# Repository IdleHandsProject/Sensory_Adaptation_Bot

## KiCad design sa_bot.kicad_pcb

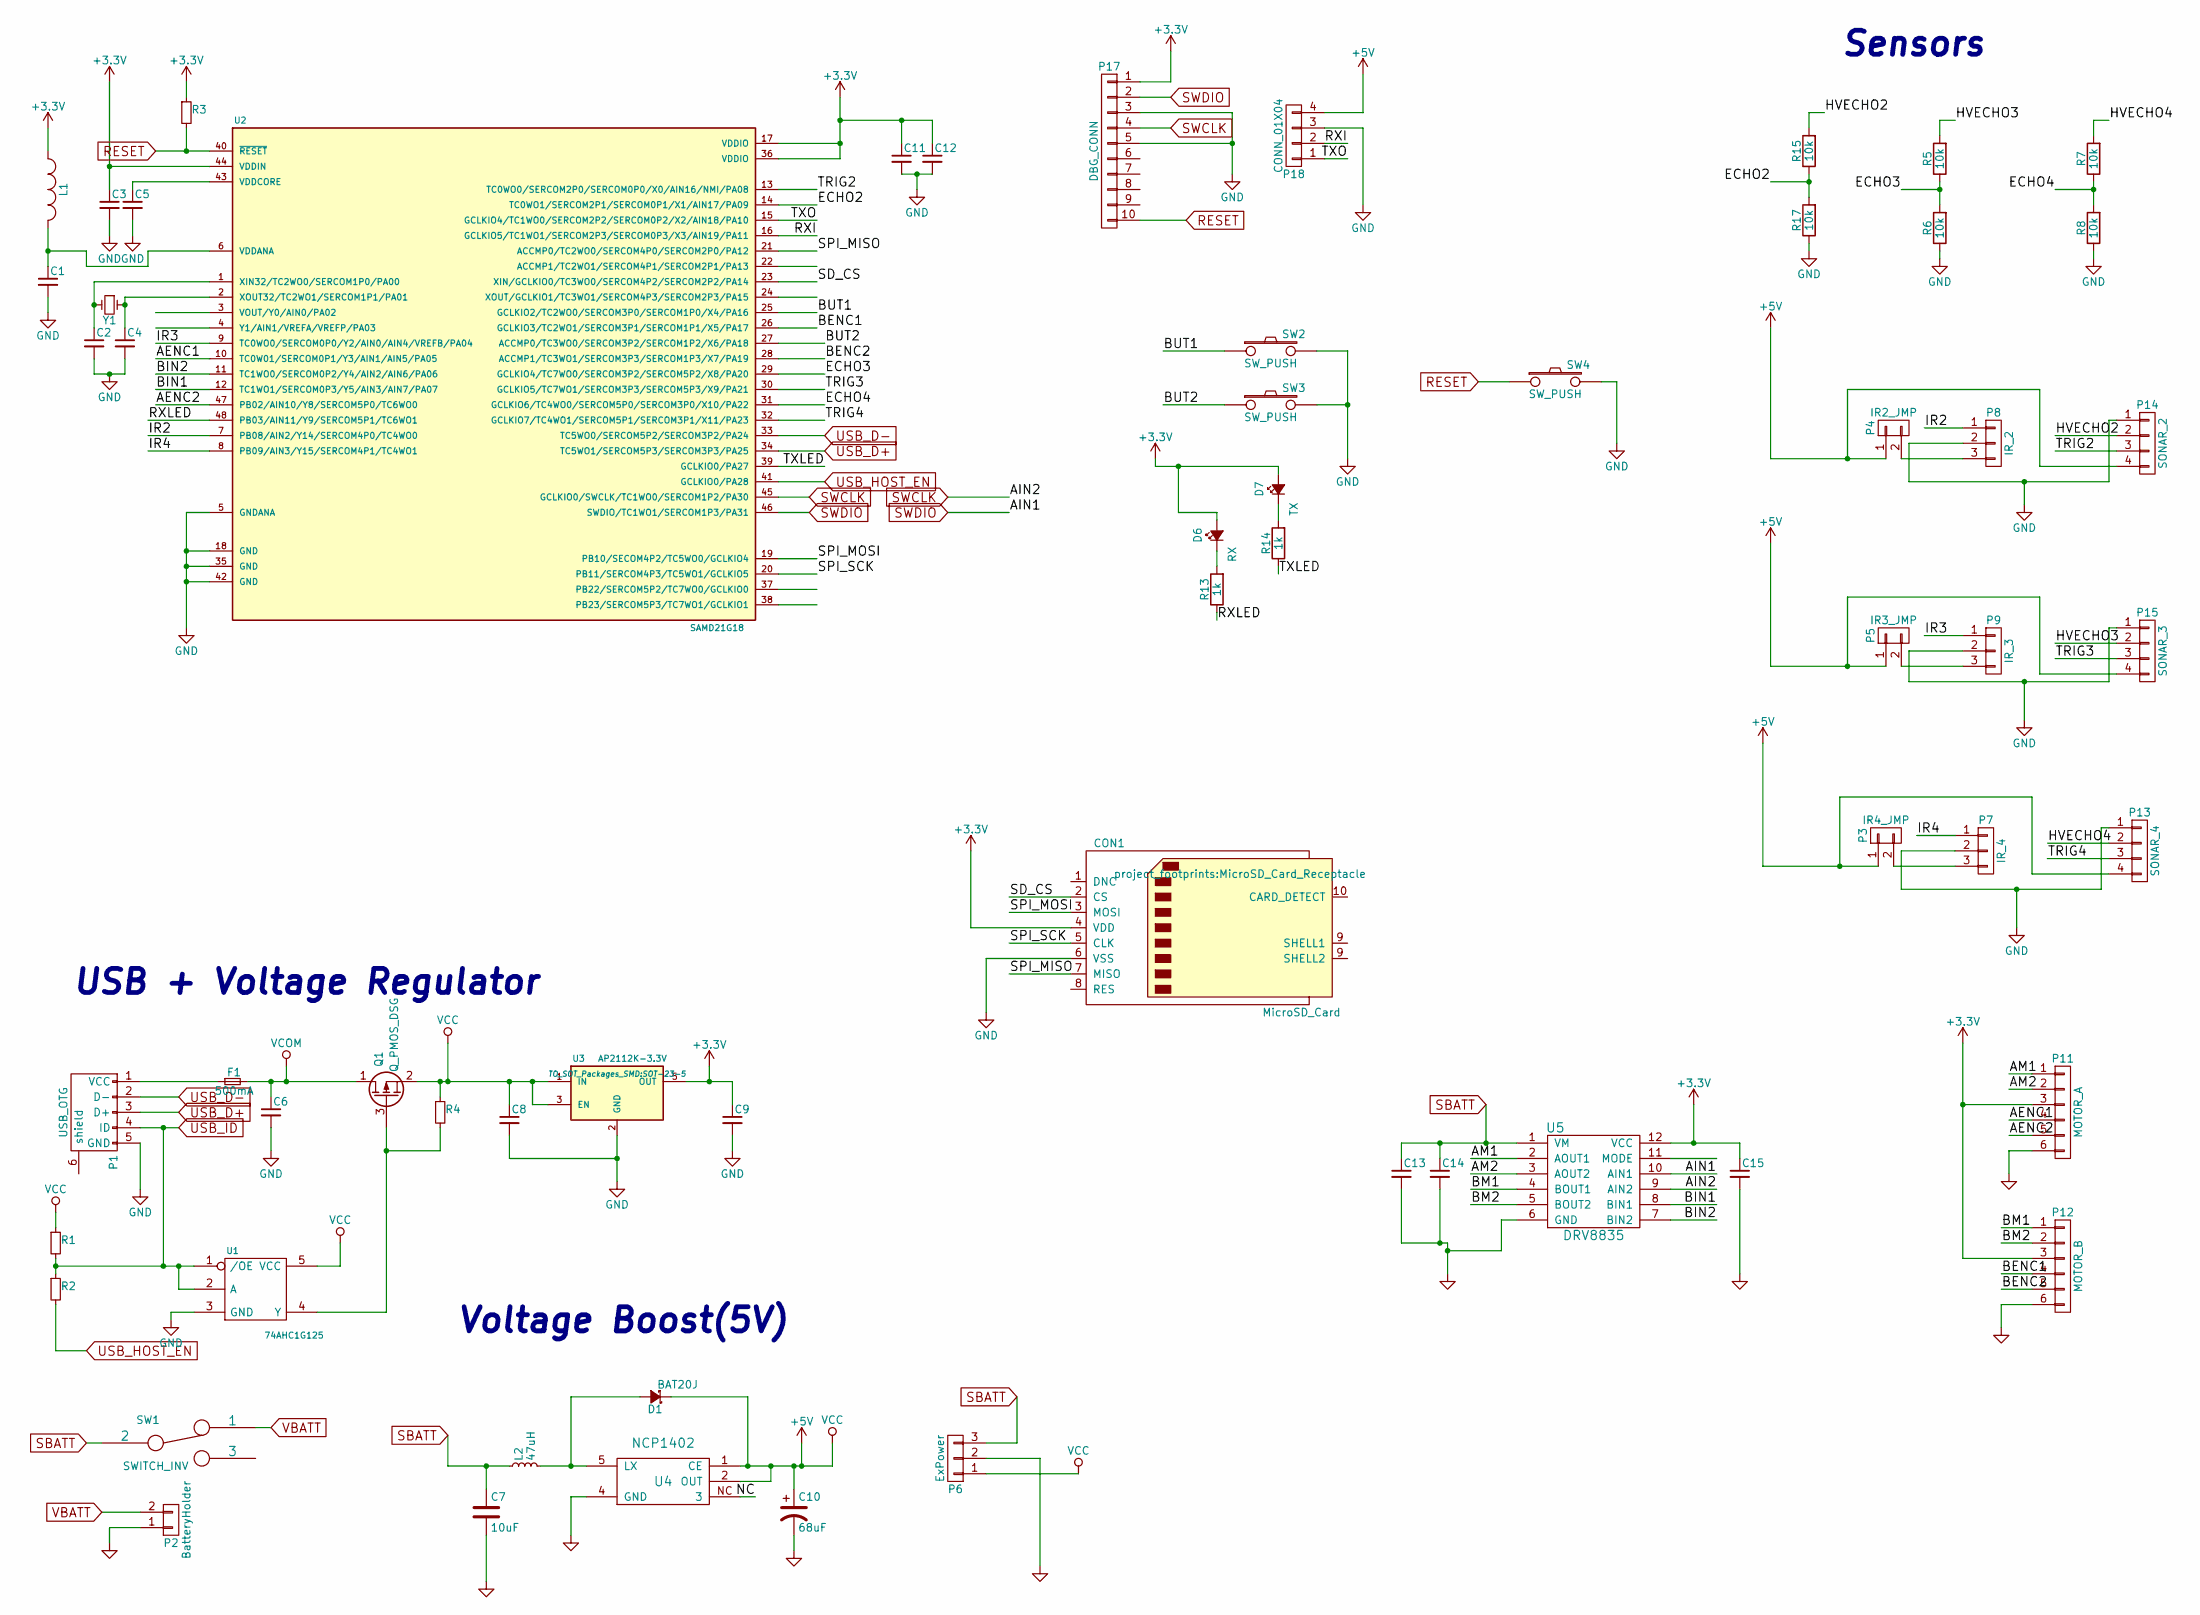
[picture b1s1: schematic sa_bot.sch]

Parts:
C1, C3, C5, C11, C12, C14, C15: 0.1uF; C_0402_Hand; Digikey Part No. 490-6328-1-ND
C2, C4: 15pF; C_0402_Hand; Digikey Part No. 712-1261-1-ND
C6: 2.2uF; C_0402_Hand; Digikey Part No. 1276-1291-1-ND
C7: 10uF; C_0402_Hand; Digikey Part No. 311-1376-1-ND
C8: 1uF; C_0402_Hand; Digikey Part No. 490-4516-1-ND
C9: 2.2uF; C_0402_Hand; Digikey Part No. 587-1059-1-ND
C10: 68uF; C_0402_Hand; Digikey Part No. P16816-1-ND
C13: 10uF; C_0402_Hand; Digikey Part No. 311-1729-1-ND
CON1: MicroSD_Card; MicroSD_Card_Receptacle; Digikey Part No. 114-00841-68-2-ND
D1: BAT20J; sod80c; Digikey Part No. 497-3381-1-ND
D6: RX; Led_0603; Digikey Part No. 160-1447-1-ND
D7: TX; Led_0603; Digikey Part No. 160-1448-1-ND
F1: 500mA; c_1206; Digikey Part No. 507-1803-1-ND
L1: FB - 30Ohm; R_SM0603; Digikey Part No. 445-2986-1-ND
L2: 47uH; I_1212; Digikey Part No. 587-2104-1-ND
P1: USB_OTG; USB_Micro-B; Digikey Part No. 609-4618-1-ND
P2: BatteryHolder; Battery_3xAAA_Holder; Digikey Part No. 36-2479-ND
P3: IR4_JMP; Pin_Header_Straight_1x02
P4: IR2_JMP; Pin_Header_Straight_1x02
P5: IR3_JMP; Pin_Header_Straight_1x02
P6: ExPower; Pin_Header_Straight_1x03
P7: IR_4; Pin_Header_Straight_1x03
P8: IR_2; Pin_Header_Straight_1x03
P9: IR_3; Pin_Header_Straight_1x03
P11: MOTOR_A; Pin_Header_Straight_1x06
P12: MOTOR_B; Pin_Header_Straight_1x06
P13: SONAR_4; Pin_Header_Straight_1x04; Digikey Part No. S5479-ND
P14: SONAR_2; Pin_Header_Straight_1x04; Digikey Part No. S5479-ND
P15: SONAR_3; Pin_Header_Straight_1x04; Digikey Part No. S5479-ND
P17: DBG_CONN; Pin_Header_Straight_2x05_Pitch1.27mm; Digikey Part No. 1175-1627-ND
P18: CONN_01X04; Pin_Header_Straight_1x04
Q1: Q_PMOS_DSG; SOT23; Digikey Part No. DMG2307L-7DICT-ND
R1: 100k; R_0402_Hand; Digikey Part No. 311-100KLRCT-ND
R2: 330; R_0402_Hand; Digikey Part No. 311-330JRCT-ND
R3, R5, R6, R7, R8, R15, R17: 10k; R_0402_Hand; Digikey Part No. 311-10KJRCT-ND
R4: 47K; R_0402_Hand; Digikey Part No. 311-47.0KLRCT-ND
R13, R14: 1k; R_0402_Hand; Digikey Part No. 311-1.0KJRCT-ND
SW1: SWITCH_INV; Pin_Header_Straight_1x03
SW2: SW_PUSH; SW_SPST_PTS645; Digikey Part No. CKN9112CT-ND
SW3: SW_PUSH; SW_SPST_PTS645; Digikey Part No. CKN9084CT-ND
SW4: SW_PUSH; SW_SPST_EVQPE1; Digikey Part No. CKN9084CT-ND
U1: 74AHC1G125; sot23-5; Digikey Part No. 568-4452-1-ND
U2: SAMD21G18; TQFP-48_7x7mm_Pitch0.5mm; Digikey Part No. ATSAMD21G18A-AU-ND
U3: AP2112K-3.3V; SOT-23-5; Digikey Part No. AP2112K-3.3TRG1DICT-ND
U4: NCP1402; sot23-5
U5: DRV8835; WSON-12-2x3; Digikey Part No. 296-30391-1-ND
Y1: Crystal_Small; crystal_smd_5x3.2mm; Digikey Part No. 535-9536-1-ND

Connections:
+3V3: C3.1, C9.1, C11.1, C12.1, C15.1, CON1.4 (VDD), D6.2 (A), D7.2 (A), L1.1, P11.3, P12.3, P17.1, R3.1, U2.17 (VDDIO), U2.36 (VDDIO), U2.44 (VDDIN), U3.5 (OUT), U5.12 (VCC)
/AENC1: P11.4, U2.10 (TC0W01/SERCOM0P1/Y3/AIN1/AIN5/PA05)
/AENC2: P11.5, U2.47 (PB02/AIN10/Y8/SERCOM5P0/TC6WO0)
/AM1: P11.1, U5.2 (AOUT1)
/AM2: P11.2, U5.3 (AOUT2)
/BENC1: P12.4, U2.26 (GCLKIO3/TC2WO1/SERCOM3P1/SERCOM1P1/X5/P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)
/BENC2: P12.5, U2.28 (ACCMP1/TC3WO1/SERCOM3P3/SERCOM1P3/X7/PA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)
/BIN1: U2.12 (TC1WO1/SERCOM0P3/Y5/AIN3/AIN7/PA07), U5.8 (BIN1)
/BIN2: U2.11 (TC1WO0/SERCOM0P2/Y4/AIN2/AIN6/PA06), U5.7 (BIN2)
/BM1: P12.1, U5.4 (BOUT1)
/BM2: P12.2, U5.5 (BOUT2)
/BUT1: SW2.1, U2.25 (GCLKIO2/TC2WO0/SERCOM3P0/SERCOM1P0/X4/P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)
/BUT2: SW3.1, U2.27 (ACCMP0/TC3WO0/SERCOM3P2/SERCOM1P2/X6/PA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)
/ECHO2: R15.1, R17.2, U2.14 (TC0WO1/SERCOM2P1/SERCOM0P1/X1/AIN17/PA09)
/ECHO3: R5.1, R6.2, U2.29 (GCLKIO4/TC7WO0/SERCOM3P2/SERCOM5P2/X8/P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)
/ECHO4: R7.1, R8.2, U2.31 (GCLKIO6/TC4WO0/SERCOM5P0/SERCOM3P0/X10/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)
/HVECHO2: P14.2, R15.2
/HVECHO3: P15.2, R5.2
/HVECHO4: P13.2, R7.2
/IR2: P8.1, U2.7 (PB08/AIN2/Y14/SERCOM4P0/TC4WO0)
/IR3: P9.1, U2.9 (TC0WO0/SERCOM0P0/Y2/AIN0/AIN4/VREFB/PA04)
/IR4: P7.1, U2.8 (PB09/AIN3/Y15/SERCOM4P1/TC4WO1)
/RXI: P18.2, U2.16 (GCLKIO5/TC1WO1/SERCOM2P3/SERCOM0P3/X3/A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)
/RXLED: R13.1, U2.48 (PB03/AIN11/Y9/SERCOM5P1/TC6WO1)
/SD_CS: CON1.2 (CS), U2.23 (XIN/GCLKIO0/TC3WO0/SERCOM4P2/SERCOM2P2/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)
/SPI_MISO: CON1.7 (MISO), U2.21 (ACCMP0/TC2WO0/SERCOM4P0/SERCOM2P0/PA12)
/SPI_MOSI: CON1.3 (MOSI), U2.19 (PB10/SECOM4P2/TC5WO0/GCLKIO4)
/SPI_SCK: CON1.5 (CLK), U2.20 (PB11/SERCOM4P3/TC5WO1/GCLKIO5)
/TRIG2: P14.3, U2.13 (TC0WO0/SERCOM2P0/SERCOM0P0/X0/AIN16/NMI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)
/TRIG3: P15.3, U2.30 (GCLKIO5/TC7WO1/SERCOM3P3/SERCOM5P3/X9/P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)
/TRIG4: P13.3, U2.32 (GCLKIO7/TC4WO1/SERCOM5P1/SERCOM3P1/X11/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)
/TXLED: R14.1, U2.39 (GCLKIO0/PA27)
/TXO: P18.1, U2.15 (GCLKIO4/TC1WO0/SERCOM2P2/SERCOM0P2/X2/A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)
GND: C1.2, C2.2, C3.2, C4.2, C5.2, C6.2, C7.2, C8.2, C9.2, C10.2, C11.2, C12.2, C13.2, C14.2, C15.2, CON1.6 (VSS), P1.5 (GND), P2.1, P6.2, P7.2, P8.2, P9.2, P11.6, P12.6, P13.1, P14.1, P15.1, P17.3, P17.5, P18.3, R6.1, R8.1, R17.1, SW2.2, SW3.2, SW4.2, U1.3 (GND), U2.5 (GNDANA), U2.18 (GND), U2.35 (GND), U2.42 (GND), U3.2 (GND), U4.4 (GND), U5.6 (GND)
unnamed: C1.1, L1.2, U2.6 (VDDANA)
unnamed: C2.1, U2.1 (XIN32/TC2WO0/SERCOM1P0/PA00), Y1.2
unnamed: C4.1, U2.2 (XOUT32/TC2WO1/SERCOM1P1/PA01), Y1.1
unnamed: C5.1, U2.43 (VDDCORE)
unnamed: D1.2 (A), L2.2, U4.5 (LX)
unnamed: D6.1 (K), R13.2
unnamed: D7.1 (K), R14.2
unnamed: F1.1, P1.1 (VCC)
unnamed: P3.2, P7.3
unnamed: P4.2, P8.3
unnamed: P5.2, P9.3
unnamed: Q1.3 (G), R4.2, U1.4 (Y)
RESET: P17.10, R3.2, SW4.1, U2.40 (~RESET~)
SBATT: C7.1, C13.1, C14.1, L2.1, P6.3, SW1.2, U5.1 (VM)
SWDIO: P17.2, U2.46 (SWDIO/TC1WO1/SERCOM1P3/PA31), U5.10 (AIN1)
USB_D+: P1.3 (D+), U2.34 (TC5WO1/SERCOM5P3/SERCOM3P3/PA25)
USB_D-: P1.2 (D-), U2.33 (TC5WO0/SERCOM5P2/SERCOM3P2/PA24)
USB_HOST_EN: R2.2, U2.41 (GCLKIO0/PA28)
USB_ID: P1.4 (ID), R1.2, R2.1, U1.1 (/OE), U1.2 (A)
VBATT: P2.2, SW1.1
VCC: C8.1, C10.1, D1.1 (K), P3.1, P4.1, P5.1, P6.1, P13.4, P14.4, P15.4, P18.4, Q1.2 (S), R1.1, R4.1, U1.5 (VCC), U3.1 (IN), U3.3 (EN), U4.1 (CE), U4.2 (OUT)
VCOM: C6.1, F1.2, Q1.1 (D)

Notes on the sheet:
USB + Voltage Regulator
Voltage Boost(5V)
Sensors

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
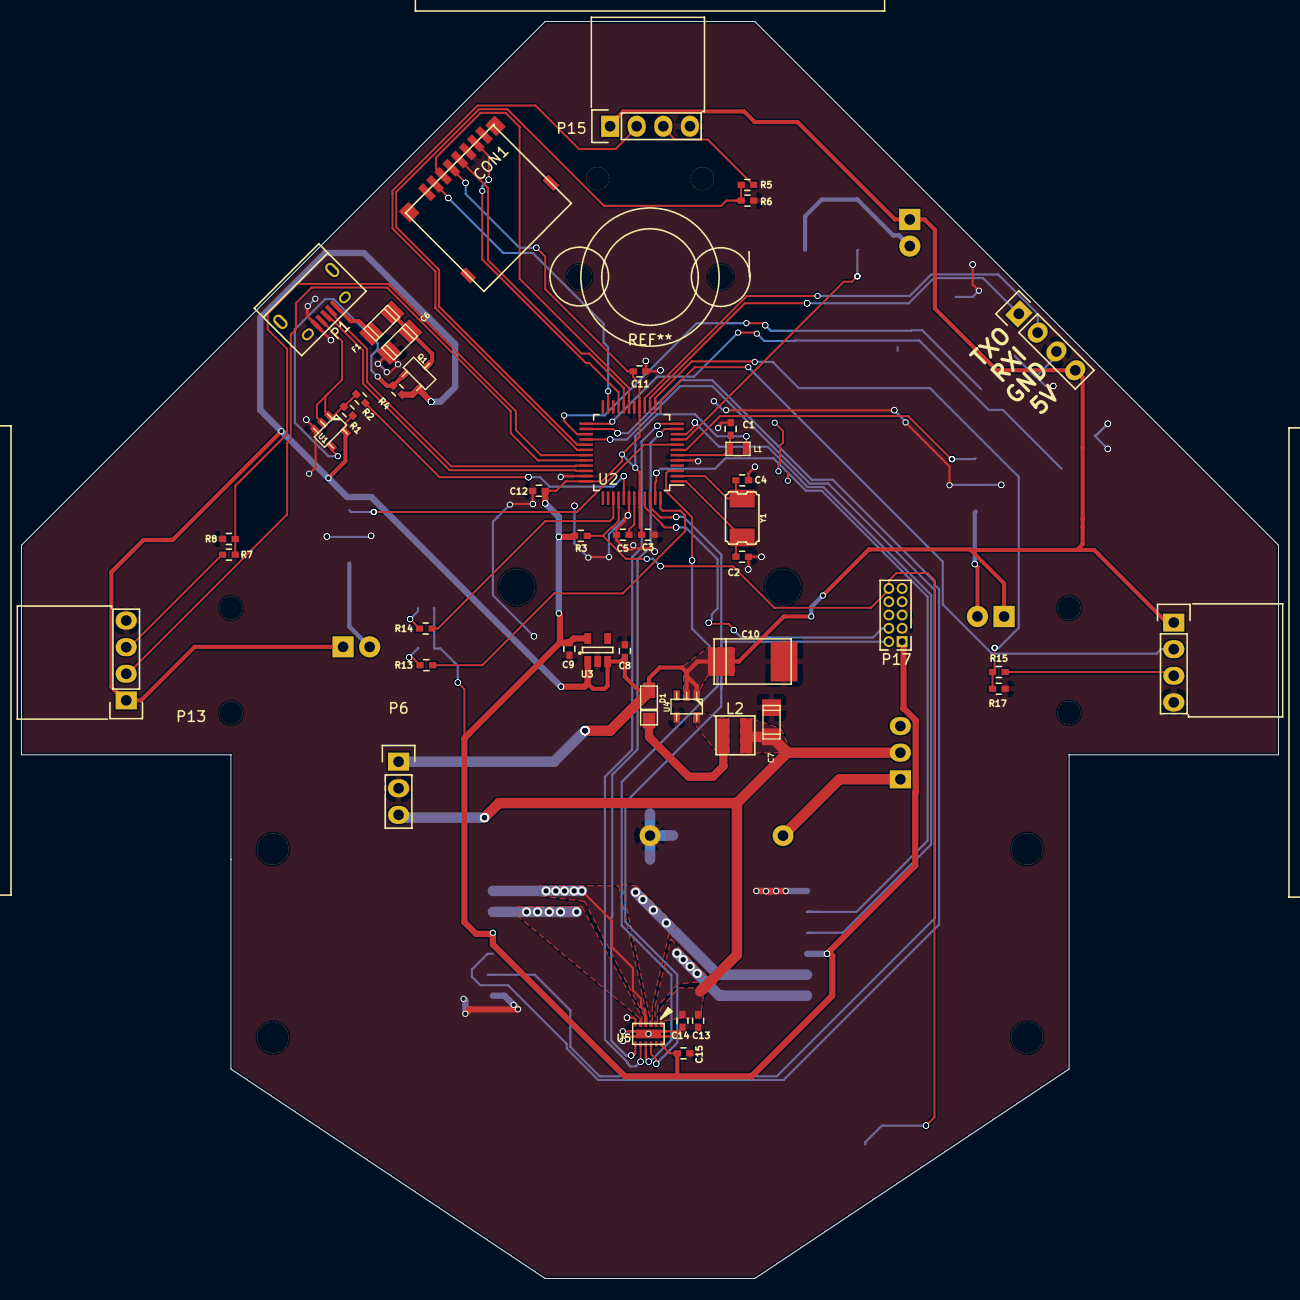
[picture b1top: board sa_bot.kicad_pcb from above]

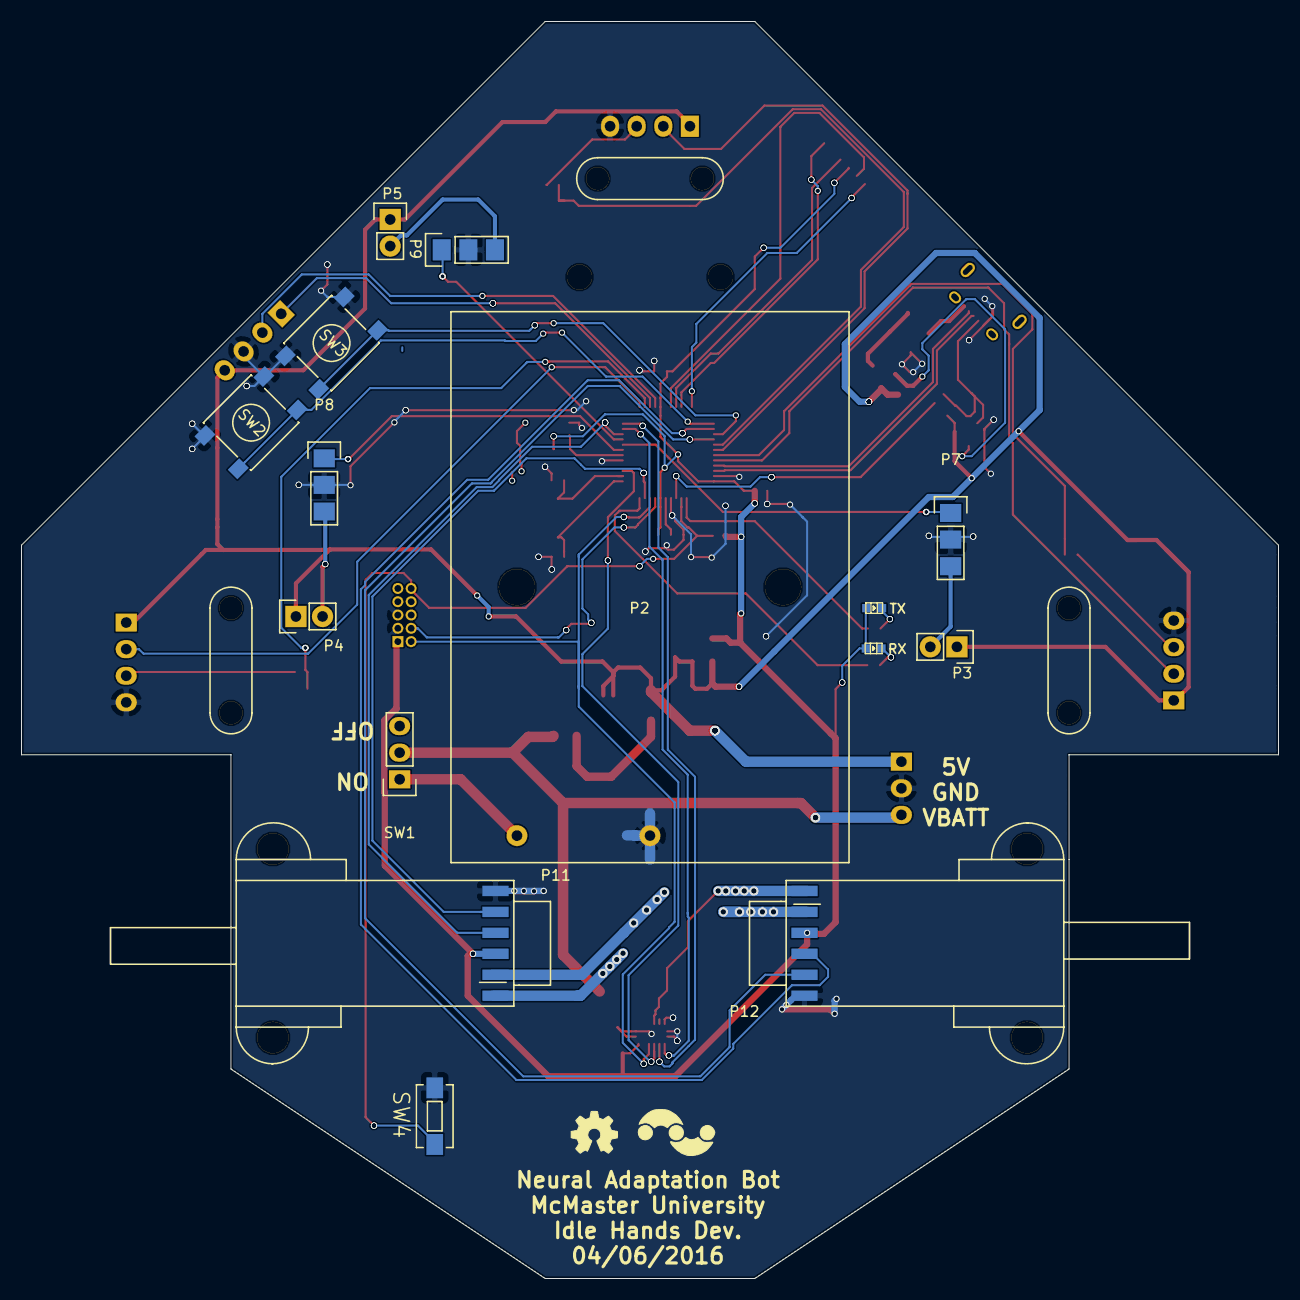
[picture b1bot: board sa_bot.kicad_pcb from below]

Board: 2 copper layers, 120.0 x 120.0 mm, 61 parts (15 on the bottom side), 58 nets.

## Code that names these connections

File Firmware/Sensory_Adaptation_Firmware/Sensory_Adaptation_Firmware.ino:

#define LED 1
//SHARP IR DISTANCE SENSORS
#define IR1 A1
#define IR2 A3
#define IR3 A2

//MOTORS ENCODERS AND CONTROL
#define AENC1 A4
#define AENC2 A5
#define BENC1 10
#define BENC2 12

#define AIN1 45
#define AIN2 44
#define BIN1 9
#define BIN2 8

//SONAR PING SENSORS
#define TRIG1 4
#define ECHO1 3
#define TRIG2 7
#define ECHO2 6
#define TRIG3 33
#define ECHO3 32

//BUTTONS
#define BUT_RED 11
#define BUT_BLUE 13


volatile int lastEncodedA = 0;
volatile long encoderValueA = 0;
long lastencoderValueA = 0;

volatile int lastEncodedB = 0;
volatile long encoderValueB = 0;
long lastencoderValueB = 0;
//int lastMSBA = 0;
//int lastLSBA = 0;

void setup() {

  pinMode(AIN1, OUTPUT);
  digitalWrite(AIN1,LOW);
  pinMode(AIN2, OUTPUT);
  digitalWrite(AIN1,LOW);
  pinMode(BIN1, OUTPUT);
  digitalWrite(BIN1,LOW);
  pinMode(BIN2, OUTPUT);
  digitalWrite(BIN2,LOW);
  motorA(0,0);
  motorB(0,0);
  
  pinMode(AENC1, INPUT);
  pinMode(AENC2, INPUT);
  pinMode(BENC1, INPUT);
  pinMode(BENC2, INPUT);

  pinMode(TRIG1, OUTPUT);
  pinMode(TRIG2, OUTPUT);
  pinMode(TRIG3, OUTPUT);
  pinMode(ECHO1, INPUT);
  pinMode(ECHO2, INPUT);
  pinMode(ECHO3, INPUT);

  pinMode(IR1, INPUT);
  pinMode(IR2, INPUT);
  pinMode(IR3, INPUT);

  pinMode(BUT_RED, INPUT_PULLUP);
  //digitalWrite(BUT_RED, HIGH);
  pinMode(BUT_BLUE, INPUT_PULLUP);
  //digitalWrite(BUT_BLUE, HIGH);

  

  
SerialUSB.begin(115200);
//while(!SerialUSB);
int BUT_REDstate = digitalRead(BUT_RED);
while(BUT_REDstate == HIGH){
  BUT_REDstate = digitalRead(BUT_RED);
  delay(50);
}
SerialUSB.println("Button Pressed");
while(BUT_REDstate == LOW){
  BUT_REDstate = digitalRead(BUT_RED);
  delay(50);
}
SerialUSB.println("Button Released");
motorA(10,1);
motorB(10,1);
delay(50);
motorA(0,0);
motorB(0,0);
delay(3000);


}

void loop() {

/*int ping1 = PING(ECHO1, TRIG1);
int ping2 = PING(ECHO2, TRIG2);
int ping3 = PING(ECHO3, TRIG3);
SerialUSB.print("Ping1: ");
SerialUSB.print(ping1);
SerialUSB.print(", Ping2: ");
SerialUSB.print(ping2);
SerialUSB.print(", Ping3: ");
SerialUSB.println(ping3);
float ReadIR1 = analogRead(IR1);
float ReadIR2 = analogRead(IR2);
float ReadIR3 = analogRead(IR3); 
SerialUSB.print("IR1: ");
SerialUSB.print(ReadIR1);
SerialUSB.print(", IR2: ");
SerialUSB.print(ReadIR2);
SerialUSB.print(", IR3: ");
SerialUSB.println(ReadIR3);
delay(1000);*/
DriveStraightStop();
delay(1000);
TurnLeftStop();
delay(1000);
TurnLeftStop();
delay(1000);
DriveStraightStop();
while(1);

}



void updateEncoderA(){
  int MSB = digitalRead(AENC1); //MSB = most significant bit
  int LSB = digitalRead(AENC2); //LSB = least significant bit

  int encoded = (MSB << 1) |LSB; //converting the 2 pin value to single number
  int sum  = (lastEncodedA << 2) | encoded; //adding it to the previous encoded value

  if(sum == 0b1100 || sum == 0b1111) encoderValueA ++;
  if(sum == 0b1101 || sum == 0b0110) encoderValueA --;

  lastEncodedA = encoded; //store this value for next time
}

void updateEncoderB(){
  int MSB = digitalRead(BENC1); //MSB = most significant bit
  int LSB = digitalRead(BENC2); //LSB = least significant bit

  int encoded = (MSB << 1) |LSB; //converting the 2 pin value to single number
  int sum  = (lastEncodedB << 2) | encoded; //adding it to the previous encoded value

  if(sum == 0b1100 || sum == 0b1111) encoderValueB ++;
  if(sum == 0b1101 || sum == 0b0110) encoderValueB --;

  lastEncodedB = encoded; //store this value for next time
}


//Percent of motor speec and direction(1/0, forward/backward);
void motorA(int percent, int dir){
  if (dir==1){
    digitalWrite(AIN1, LOW);
    int drive = map(percent, 0, 100, 170, 255);
    analogWrite(AIN2, drive);
  }
  if (dir==0){
    digitalWrite(AIN2, LOW);
    int drive = map(percent, 0, 100, 170, 255);
    analogWrite(AIN1, drive);
  }
  if (percent<1){
    digitalWrite(AIN1, LOW);
    digitalWrite(AIN2, LOW);
  }
}

void motorB(int percent, int dir){
  if (dir==0){
    digitalWrite(BIN1, LOW);
    int drive = map(percent, 0, 100, 170, 255);
    analogWrite(BIN2, drive);
  }
  if (dir==1){
    digitalWrite(BIN2, LOW);
    int drive = map(percent, 0, 100, 170, 255);
    analogWrite(BIN1, drive);
  }
  if (percent<1){
    digitalWrite(BIN1, LOW);
    digitalWrite(BIN2, LOW);
  }
}

void DriveStraightStop(){
  attachInterrupt(AENC1, updateEncoderA, CHANGE); 
  //attachInterrupt(AENC2, updateEncoderA, CHANGE);
  //attachInterrupt(BENC1, updateEncoderB, CHANGE); 
  attachInterrupt(BENC2, updateEncoderB, CHANGE);
  int distance = PING(ECHO2, TRIG2);
  
  int mA = 15;
  int mB = 15;
  int mRateA = 150;
  int mRateB = 150;
  encoderValueA = 0;
  encoderValueB = 0;
  while(distance > 10){
    motorA(mA, 1);
    motorB(mB, 1);
    if (encoderValueA > encoderValueB){
      mRateA--;
      mRateB++;
    }
    if (encoderValueA < encoderValueB){
      mRateB--;
      mRateA++;
    }
    mA = mRateA / 10;
    mB = mRateB / 10;
    mA = constrain(mA,0,25);
     mB = constrain(mB,0,25);
     //SerialUSB.print(mRateA);
     //SerialUSB.print(", ");
     //SerialUSB.println(mRateB);
     SerialUSB.print(encoderValueA);
     SerialUSB.print(", ");
     SerialUSB.println(encoderValueB);
    delay(50);
    distance = PING(ECHO2,TRIG2);
  }
  motorA(0,0);
  motorB(0,0);
}

void TurnLeftStop(){
  attachInterrupt(AENC1, updateEncoderA, CHANGE); 
  //attachInterrupt(AENC2, updateEncoderA, CHANGE);
  //attachInterrupt(BENC1, updateEncoderB, CHANGE); 
  attachInterrupt(BENC2, updateEncoderB, CHANGE);
  encoderValueA = 0;
  encoderValueB = 0;
  while(encoderValueA > -60 || encoderValueB < 70){
  if (encoderValueA > -60){
   motorA(15, 0); 
  }
  else{
    motorA(0,0);
  }
  if (encoderValueB < 70){
   motorB(15, 1); 
  }
  else{
    motorB(0,0);
  }
  SerialUSB.print(encoderValueA);
     SerialUSB.print(", ");
     SerialUSB.println(encoderValueB);
  }
  motorA(0,0);
  motorB(0,0);
}

int getRPM_A(){
  attachInterrupt(AENC1, updateEncoderA, CHANGE); 
  attachInterrupt(AENC2, updateEncoderA, CHANGE);
  int encoderA_S = 0;
  int encoderA_F = 0;
  encoderA_S = encoderValueA;
  delay(10);
  encoderA_F = encoderValueA;
  int change = encoderA_F - encoderA_S;
  int rpm = ((change/12) * 100 * 60)/26;
  return change;
  detachInterrupt(AENC1);
  detachInterrupt(BENC1);
}

void motorA_RPM(int rpm, int dir){

  attachInterrupt(AENC1, updateEncoderA, CHANGE); 
  attachInterrupt(AENC2, updateEncoderA, CHANGE);
  int timeS,timeE = 0;
  int encoderA_S = 0;
  int encoderA_F = 0;
  
  
  encoderA_S = encoderValueA;
  delay(10);

  
}


unsigned long PING(int echoPin, int trigPin)
{ 
   // Switch signalpin to output
  pinMode(trigPin,OUTPUT);
  digitalWrite(trigPin, LOW); // Send low pulse 
  delayMicroseconds(2); // Wait for 2 microseconds
  digitalWrite(trigPin, HIGH); // Send high pulse
  delayMicroseconds(5); // Wait for 5 microseconds
  digitalWrite(trigPin, LOW); // Holdoff
  pinMode(trigPin, INPUT);
  //pinMode(trigpin, HIGH);
   // Turn on pullup resistor
  // please note that pulseIn has a 1sec timeout, which may
  // not be desirable. Depending on your sensor specs, you
  // can likely bound the time like this -- marcmerlin
  // echo = pulseIn(ultraSoundSignal, HIGH, 38000)
  unsigned long echo = pulseIn(echoPin, HIGH,30000); //Listen for echo
  unsigned long ultrasoundValue = (echo / 58.138);// * .39; //convert to CM then to inches
  return ultrasoundValue;
  
}

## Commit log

2016-07-15 Moved RXTX LEDs
2016-07-15 Added Reset Button
2016-07-15 Fixed encoder Interrupt
2016-07-16 Moved Motor from SWCLK to A0
2016-12-03 V002 and firmware
2016-12-03 Remove PSD
